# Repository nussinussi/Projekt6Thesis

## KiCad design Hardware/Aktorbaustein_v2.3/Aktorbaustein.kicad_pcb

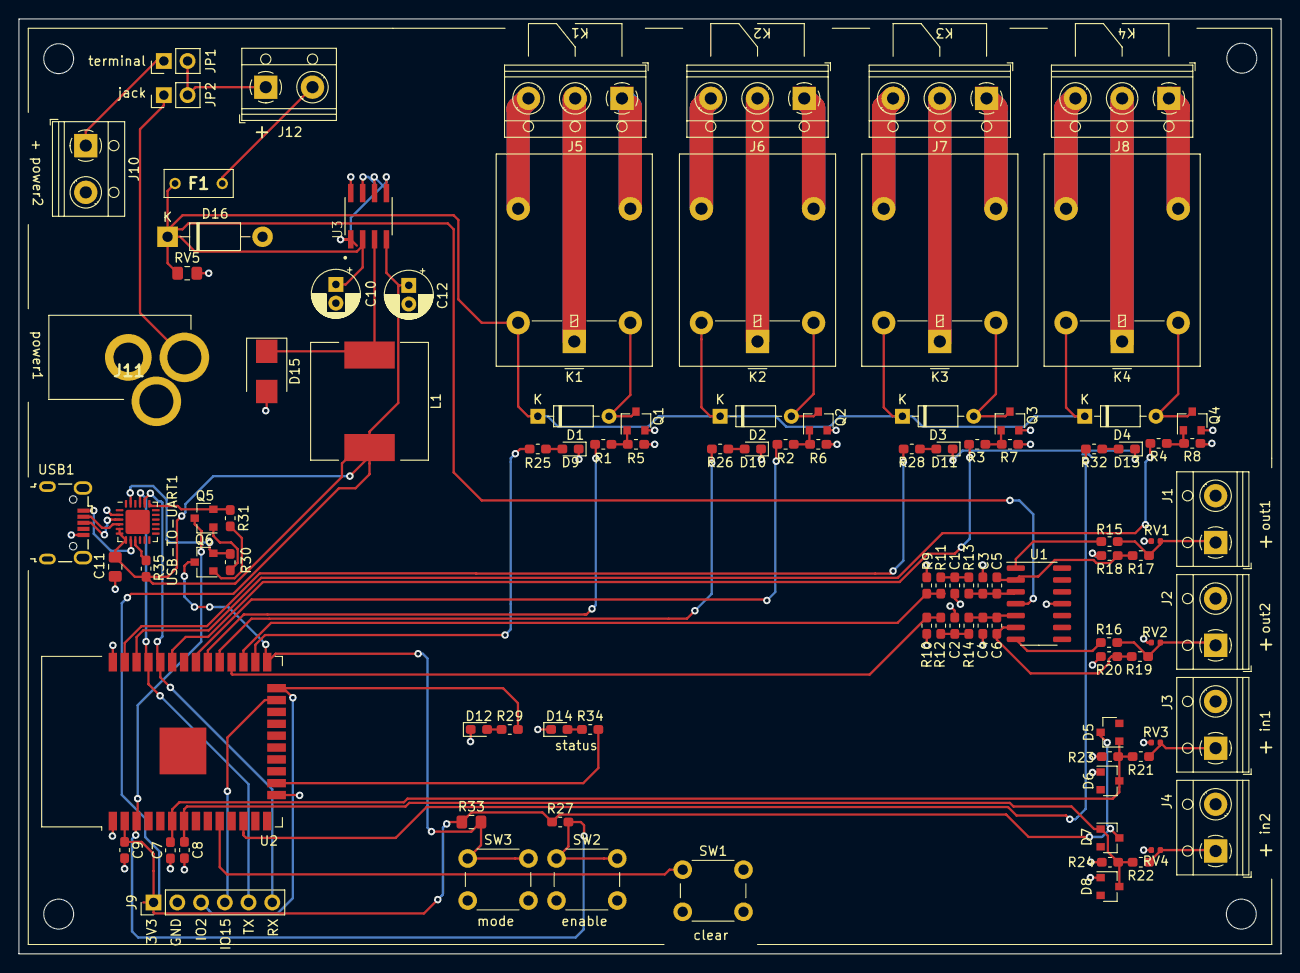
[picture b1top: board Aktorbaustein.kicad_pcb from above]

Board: 2 copper layers, 135.0 x 100.0 mm, 106 parts (0 on the bottom side), 74 nets.

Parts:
C1, C2, C7, C8: 100nF; C_0603_1608Metric_Pad1.05x0.95mm_HandSolder
C3, C4: 10nF; C_0603_1608Metric_Pad1.05x0.95mm_HandSolder
C5, C6: 1n; C_0603_1608Metric_Pad1.05x0.95mm_HandSolder
C9: 10uF; C_0603_1608Metric_Pad1.05x0.95mm_HandSolder
C10, C12: 15uF; CP_Radial_D5.0mm_P2.00mm
C11: 10uF; C_0805_2012Metric_Pad1.15x1.40mm_HandSolder
D1, D2, D3, D4: 1N4148; D_DO-35_SOD27_P7.62mm_Horizontal
D5, D6, D7, D8: BAT54; D_SOT-23_ANK
D9, D10, D11, D13: 150060VS55040; LED_0603_1608Metric_Pad1.05x0.95mm_HandSolder
D12: 150060BS55040; LED_0603_1608Metric_Pad1.05x0.95mm_HandSolder
D14: 150060RS75000; LED_0603_1608Metric_Pad1.05x0.95mm_HandSolder
D15: B260; D_SMB
D16: 1N4001G; D_DO-41_SOD81_P10.16mm_Horizontal
F1: RXEF020-AP; RXEF0252
H1, H2, H3, H4: MountingHole; MountingHole_3.2mm_M3_ISO7380
J1, J2, J3, J4: TB001-500-02BE; TerminalBlock_RND_205-00012_1x02_P5.00mm_Horizontal
J5, J6, J7, J8: TB002-500-03BE; TerminalBlock_RND_205-00013_1x03_P5.00mm_Horizontal
J9: Conn_01x06_Male; PinHeader_1x06_P2.54mm_Vertical
J10: TB003V-500-P02BE; TerminalBlock_RND_205-00012_1x02_P5.00mm_Horizontal
J11: CON-SOCJ-2155; CONSOCJ2155
J12: Screw_Terminal_01x02; TerminalBlock_RND_205-00012_1x02_P5.00mm_Horizontal
JP1, JP2: Jumper; PinHeader_1x02_P2.54mm_Vertical
K1, K2, K3, K4: G5LE-1-VD DC24; Relay_SPDT_Omron-G5LE-1
L1: SRR1260-681K; L_12x12mm_H6mm
Q1, Q2, Q3, Q4: BSS123; SOT-23
Q5, Q6: MMBT3904; SOT-23
R1, R2, R3, R4: 330; R_0603_1608Metric_Pad1.05x0.95mm_HandSolder
R5, R6, R7, R8: 100k; R_0603_1608Metric_Pad1.05x0.95mm_HandSolder
R9, R10, R15, R16, R18, R20, R27, R30, R31, R35: 10k; R_0603_1608Metric_Pad1.05x0.95mm_HandSolder
R11, R12: 3.9k; R_0603_1608Metric_Pad1.05x0.95mm_HandSolder
R13, R14: 39k; R_0603_1608Metric_Pad1.05x0.95mm_HandSolder
R17, R19: 22k; R_0603_1608Metric_Pad1.05x0.95mm_HandSolder
R21, R22: 47k; R_0603_1608Metric_Pad1.05x0.95mm_HandSolder
R23, R24: 20k; R_0603_1608Metric_Pad1.05x0.95mm_HandSolder
R25, R26, R28, R29, R32, R34: 200; R_0603_1608Metric_Pad1.05x0.95mm_HandSolder
R33: 10k; R_0805_2012Metric_Pad1.15x1.40mm_HandSolder
RV1, RV2, RV3, RV4: CG0402MLA-14LG; R_0402_1005Metric
RV5: AVRM2012C330KT801N; R_0805_2012Metric_Pad1.15x1.40mm_HandSolder
SW1, SW2, SW3: SKHHALA010; SW_PUSH_6mm_H4.3mm
U1: LM324A; SOIC-14_3.9x8.7mm_P1.27mm
U2: ESP32-WROOM-32
U3: MIC4680-3.3YM-TR; SOIC127P600X175-8N
USB1: USB_B_Micro; USB_Micro-B_Wuerth_629105150521
USB-TO-UART1: CP2104; QFN-24-1EP_4x4mm_P0.5mm_EP2.6x2.6mm

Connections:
+3V3: C9.1, C11.1, C12.1, D5.1, D7.1, J9.1, L1.2, R27.1, R33.1, R35.1, U2.2, U3.4, USB-TO-UART1.5, USB-TO-UART1.6, USB-TO-UART1.7
+24V: C10.1, D1.1, D2.1, D3.1, D4.1, D16.1, F1.1, K1.5, K2.5, K3.5, K4.5, RV5.1, U1.4, U3.2
/Logik/24V_F1: F1.2, J12.2
/Logik/24V_jack: J11.1, JP2.1
/Logik/24V_terminal: J10.1, JP1.1
/Logik/LED1: D9.2, R25.1
/Logik/LED2: D10.2, R26.1
/Logik/LED3: D11.2, R28.1
/Logik/LED4: D13.2, R32.1
/Logik/LED5: D12.2, R29.1
/Logik/LED6: D14.2, R34.1
/Schnittstellen/K1_1: J5.2, K1.1
/Schnittstellen/K1_3: J5.1, K1.3
/Schnittstellen/K1_4: J5.3, K1.4
/Schnittstellen/K2_1: J6.2, K2.1
/Schnittstellen/K2_3: J6.1, K2.3
/Schnittstellen/K2_4: J6.3, K2.4
/Schnittstellen/K3_1: J7.2, K3.1
/Schnittstellen/K3_3: J7.1, K3.3
/Schnittstellen/K3_4: J7.3, K3.4
/Schnittstellen/K4_1: J8.2, K4.1
/Schnittstellen/K4_3: J8.1, K4.3
/Schnittstellen/K4_4: J8.3, K4.4
AD1: C7.1, D5.2, D6.1, R21.2, R23.1, U2.6
AD2: C8.1, D7.2, D8.1, R22.2, R24.1, U2.7
CHIP_PU: Q5.3, R27.2, SW2.1, U2.3
D+: USB1.3, USB-TO-UART1.3
D-: USB1.2, USB-TO-UART1.4
DTR: Q6.2, R30.1, USB-TO-UART1.23
GND: C1.2, C2.2, C3.2, C4.2, C7.2, C8.2, C9.2, C10.2, C11.2, C12.2, D6.2, D8.2, D9.1, D10.1, D11.1, D12.1, D13.1, D14.1, D15.2, D16.2, J1.2, J2.2, J3.2, J4.2, J9.2, J10.2, J11.2, Q1.2, Q2.2, Q3.2, Q4.2, R5.2, R6.2, R7.2, R8.2, R9.2, R10.2, R18.2, R20.2, R23.2, R24.2, RV1.2, RV2.2, RV3.2, RV4.2, RV5.2, SW1.2, SW2.2, SW3.2, U1.11, U2.1, U2.15, U2.38, U3.1, U3.5, U3.6, U3.7, U3.8, USB1.5, USB1.6, USB-TO-UART1.2
GPIO_0: Q6.3, R33.2, SW3.1, U2.25
GPIO_2: J9.3, R29.2, U2.24
GPIO_15: J9.4, U2.23
K1: R1.2, U2.30
K2: R2.2, U2.31
K3: R3.2, U2.33
K4: R4.2, U2.36
LED_1: R25.2, U2.26
LED_2: R26.2, U2.29
LED_3: R28.2, U2.37
LED_4: R32.2, U2.12
unnamed: C1.1, R11.1, R13.2
unnamed: C2.1, R12.1, R14.2
unnamed: C3.1, C5.1, R13.1, U1.3
unnamed: C4.1, C6.1, R14.1, U1.5
unnamed: C5.2, R17.2, R18.1, U1.2
unnamed: C6.2, R19.2, R20.1, U1.6
unnamed: D1.2, K1.2, Q1.3
unnamed: D2.2, K2.2, Q2.3
unnamed: D3.2, K3.2, Q3.3
unnamed: D4.2, K4.2, Q4.3
unnamed: D15.1, L1.1, U3.3
unnamed: J12.1, JP1.2, JP2.2
unnamed: Q1.1, R1.1, R5.1
unnamed: Q2.1, R2.1, R6.1
unnamed: Q3.1, R3.1, R7.1
unnamed: Q4.1, R4.1, R8.1
unnamed: Q5.1, R30.2
unnamed: Q6.1, R31.2
unnamed: R15.2, U1.1
unnamed: R16.2, U1.7
unnamed: R35.2, USB-TO-UART1.9
RTS: Q5.2, R31.1, USB-TO-UART1.19
RXD: J9.6, U2.34, USB-TO-UART1.20
Status: R34.2, U2.16
SysReset: SW1.1, U2.10
TXD: J9.5, U2.35, USB-TO-UART1.21
VBUS: USB1.1, USB-TO-UART1.8
in1: J3.1, R21.1, RV3.1
in2: J4.1, R22.1, RV4.1
out1: J1.1, R15.1, R17.1, RV1.1
out2: J2.1, R16.1, R19.1, RV2.1
pwm1: R9.1, R11.2, U2.27
pwm2: R10.1, R12.2, U2.28

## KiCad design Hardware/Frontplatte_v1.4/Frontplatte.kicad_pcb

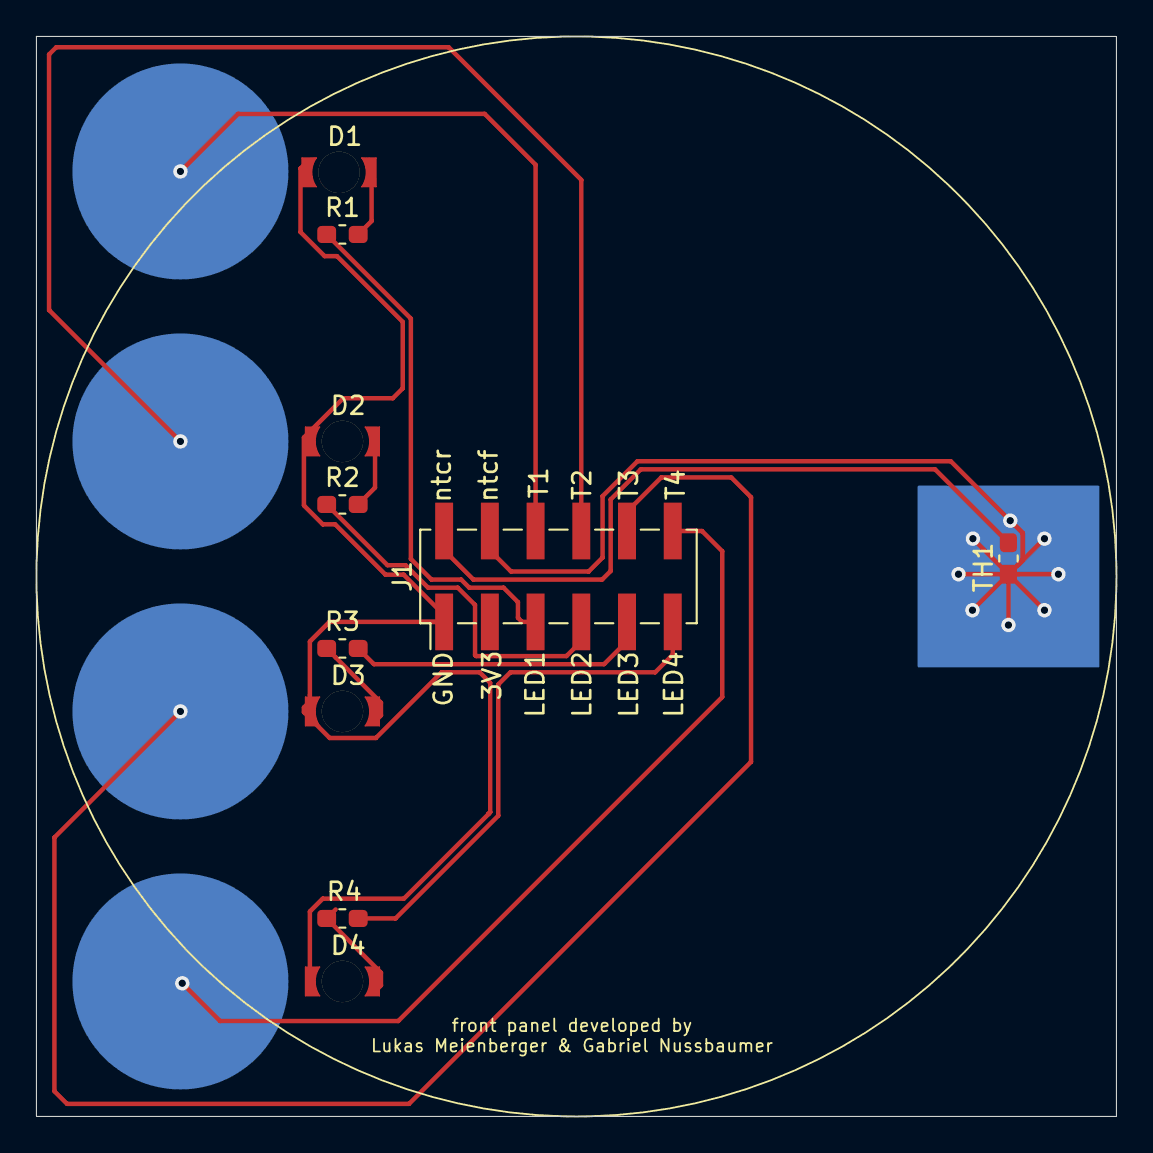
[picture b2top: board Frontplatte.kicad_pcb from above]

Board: 2 copper layers, 60.0 x 60.0 mm, 14 parts (0 on the bottom side), 11 nets.

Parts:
D1, D2, D3, D4: 156120RS75000; reverse_mounted_LED_hole_2.3mm
J1: 61000621121; PinHeader_2x06_P2.54mm_Vertical_SMD
R1, R2, R3, R4: 100; R_0603_1608Metric_Pad1.05x0.95mm_HandSolder
TA1, TA2, TA3, TA4: touch_area_round_12mm; touch_area
TH1: NCU18WF104J60RB; R_0603_1608Metric_Pad1.05x0.95mm_HandSolder

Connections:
GND: D1.1, D2.1, D3.1, D4.1, J1.1
LED1: J1.5, R1.2
LED2: J1.7, R2.2
LED3: J1.9, R3.2
LED4: J1.11, R4.2
unnamed: D1.2, R1.1
unnamed: D2.2, R2.1
unnamed: D3.2, R3.1
unnamed: D4.2, R4.1
ntcf: J1.4, TH1.1
ntcr: J1.2, TH1.2
